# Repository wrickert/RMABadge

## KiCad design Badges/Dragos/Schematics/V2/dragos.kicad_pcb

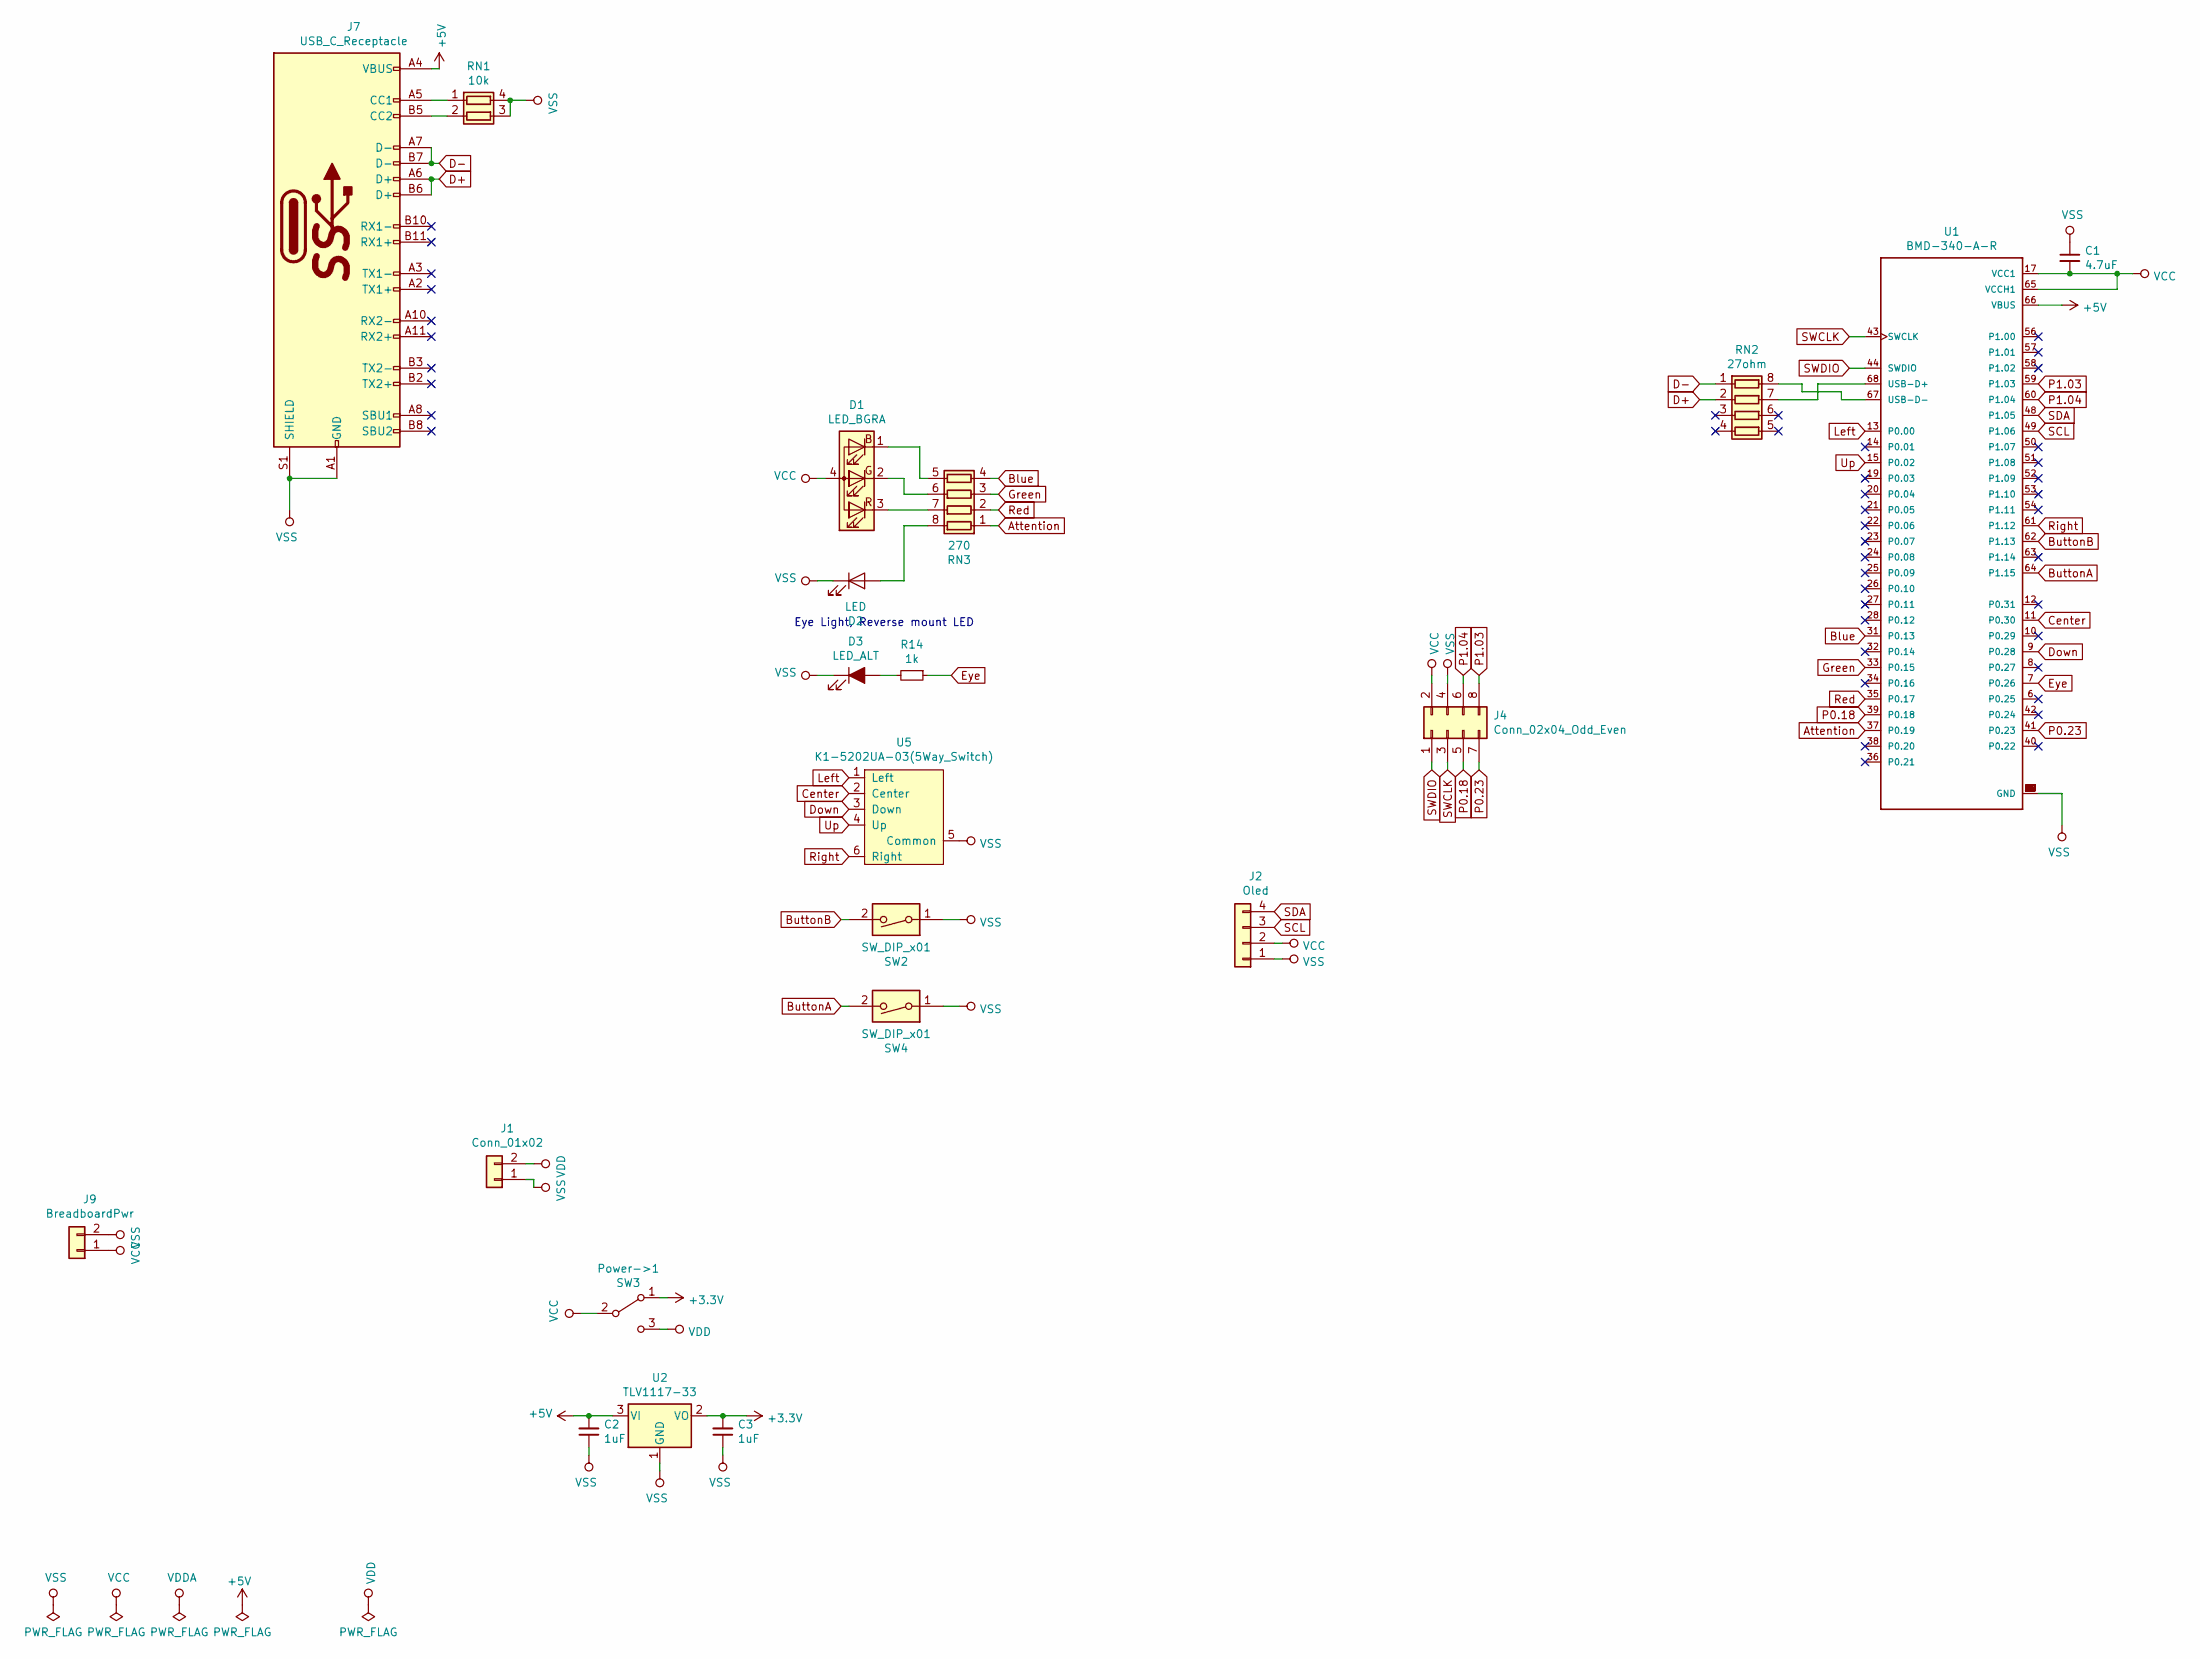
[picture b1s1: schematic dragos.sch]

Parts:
C1: 4.7uF; C_0805_2012Metric
C2, C3: 1uF; C_0805_2012Metric
D1: LED_BGRA; EKINGLUX-E6
D2: LED; LED_0603_1608Metric
D3: LED_ALT; T776-ReverseMountLED
J1: Conn_01x02
J2: Oled
J4: Conn_02x04_Odd_Even; PinHeader_2x04_P2.54mm_Vertical
J7: USB_C_Receptacle; USB_C_Receptical-Jing
J9: BreadboardPwr; PinHeader_1x02_P2.54mm_Vertical
Power->1: SW3; SK-3296S_switch
R14: 1k; R_0805_2012Metric
RN1: 10k; R_Array_Concave_2x0603
RN2: 27ohm; R_Array_Convex_4x0603
RN3: 270; R_Array_Convex_4x0603
SW2, SW4: SW_DIP_x01; 1TS002E-2500-2500-CT-HYP-Button
U1: BMD-340-A-R; RIGADO_BMD-340-A-R
U2: TLV1117-33; SOT-223-3_TabPin2
U5: K1-5202UA-03(5Way_Switch); K1-5202UA-03(5way-switch)

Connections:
+3V3: C3.2, Power->1.1 (A), U2.2 (VO)
+5V: C2.2, J7.A4 (VBUS), J7.A9 (VBUS), J7.B4 (VBUS), J7.B9 (VBUS), U1.66 (VBUS), U2.3 (VI)
Attention: RN3.1 (R1.1), U1.37 (P0.19)
Blue: RN3.4 (R4.1), U1.31 (P0.13)
ButtonA: SW4.2, U1.64 (P1.15)
ButtonB: SW2.2, U1.62 (P1.13)
Center: U1.11 (P0.30), U5.2 (Center)
D+: J7.A6 (D+), J7.B6 (D+), RN2.2 (R2.1)
D-: J7.A7 (D-), J7.B7 (D-), RN2.1 (R1.1)
Down: U1.9 (P0.28), U5.3 (Down)
Eye: R14.1, U1.7 (P0.26)
Green: RN3.3 (R3.1), U1.33 (P0.15)
Left: U1.13 (P0.00), U5.1 (Left)
unnamed: D1.1 (BK), RN3.5 (R4.2)
unnamed: D1.2 (GK), RN3.6 (R3.2)
unnamed: D1.3 (RK), RN3.7 (R2.2)
unnamed: D2.2 (A), RN3.8 (R1.2)
unnamed: D3.2 (A), R14.2
unnamed: J7.A5 (CC1), RN1.1 (R1.1)
unnamed: J7.B5 (CC2), RN1.2 (R2.1)
unnamed: RN2.7 (R2.2), U1.68 (USB-D+)
unnamed: RN2.8 (R1.2), U1.67 (USB-D-)
P0.18: J4.5, U1.39 (P0.18)
P0.23: J4.7, U1.41 (P0.23)
P1.03: J4.8, U1.59 (P1.03)
P1.04: J4.6, U1.60 (P1.04)
Red: RN3.2 (R2.1), U1.35 (P0.17)
Right: U1.61 (P1.12), U5.6 (Right)
SCL: J2.3, U1.49 (P1.06)
SDA: J2.4, U1.48 (P1.05)
SWCLK: J4.3, U1.43 (SWCLK)
SWDIO: J4.1, U1.44 (SWDIO)
Up: U1.15 (P0.02), U5.4 (Up)
VCC: C1.2, D1.4 (A), J2.2, J4.2, J9.1, Power->1.2 (B), U1.17 (VCC1), U1.65 (VCCH1)
VDD: J1.2, Power->1.3 (C)
VSS: C1.1, C2.1, C3.1, D2.1 (K), D3.1 (K), J1.1, J2.1, J4.4, J7.A1 (GND), J7.A12 (GND), J7.B1 (GND), J7.B12 (GND), J7.S1 (SHIELD), J9.2, RN1.3 (R2.2), RN1.4 (R1.2), SW2.1, SW4.1, U1.1 (GND), U1.2 (GND), U1.3 (GND), U1.4 (GND), U1.5 (GND), U1.16 (GND), U1.18 (GND), U1.29 (GND), U1.30 (GND), U1.45 (GND), U1.46 (GND), U1.47 (GND), U1.55 (GND), U2.1 (GND), U5.5 (Common)

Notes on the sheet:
Eye Light, Reverse mount LED

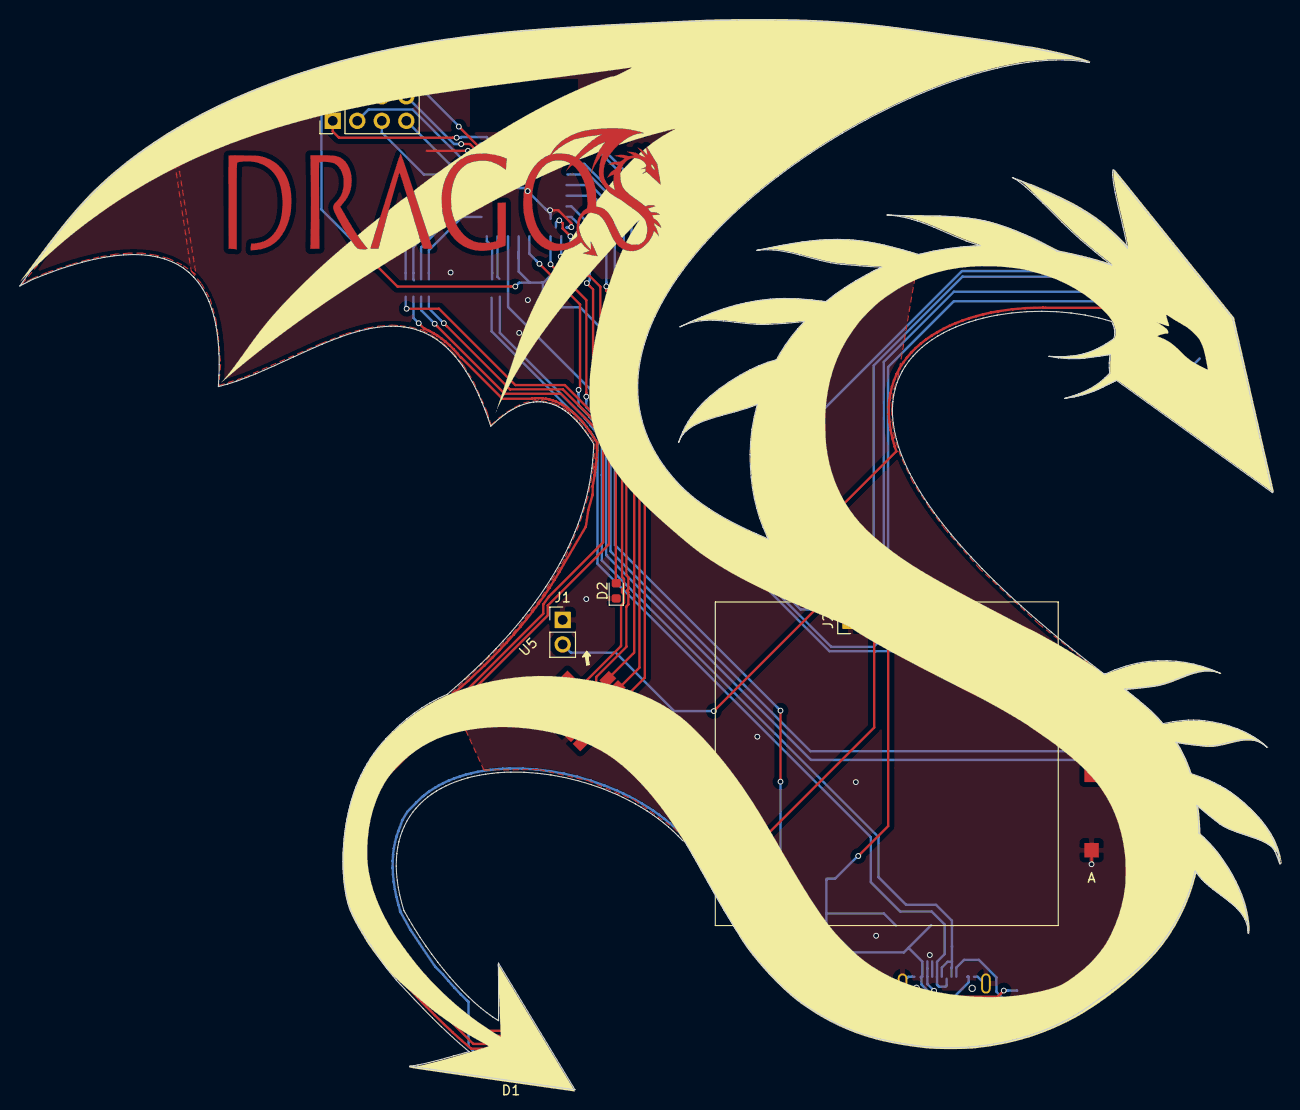
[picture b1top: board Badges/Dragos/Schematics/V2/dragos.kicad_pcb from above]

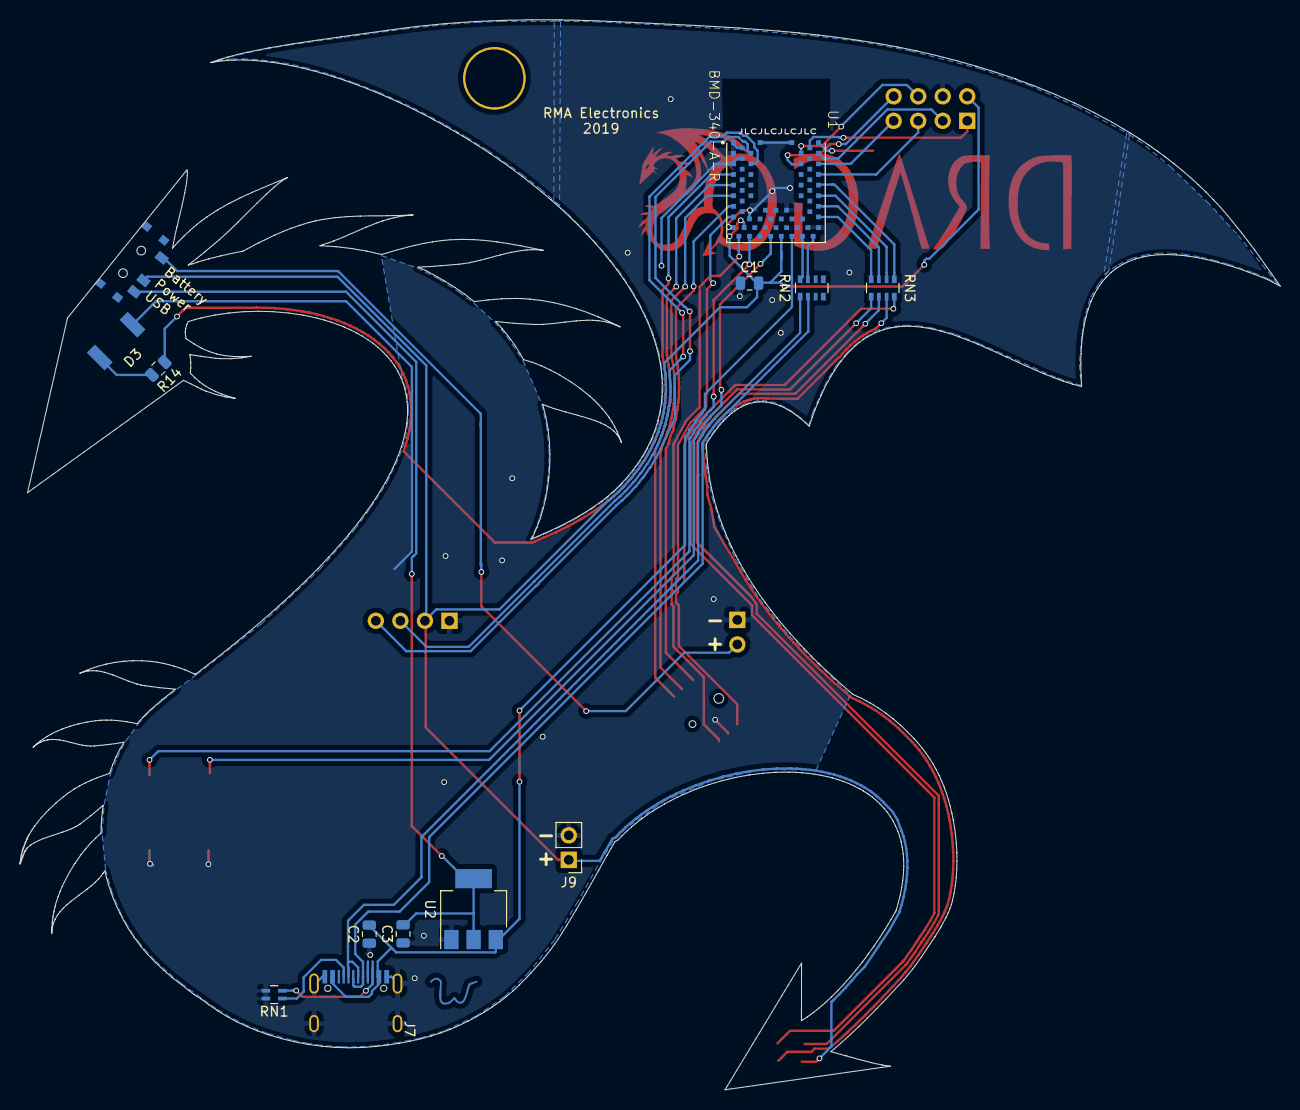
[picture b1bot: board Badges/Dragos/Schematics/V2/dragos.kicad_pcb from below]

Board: 2 copper layers, 130.4 x 110.8 mm, 22 parts (14 on the bottom side), 36 nets.

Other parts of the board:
Ref**: Val**; W

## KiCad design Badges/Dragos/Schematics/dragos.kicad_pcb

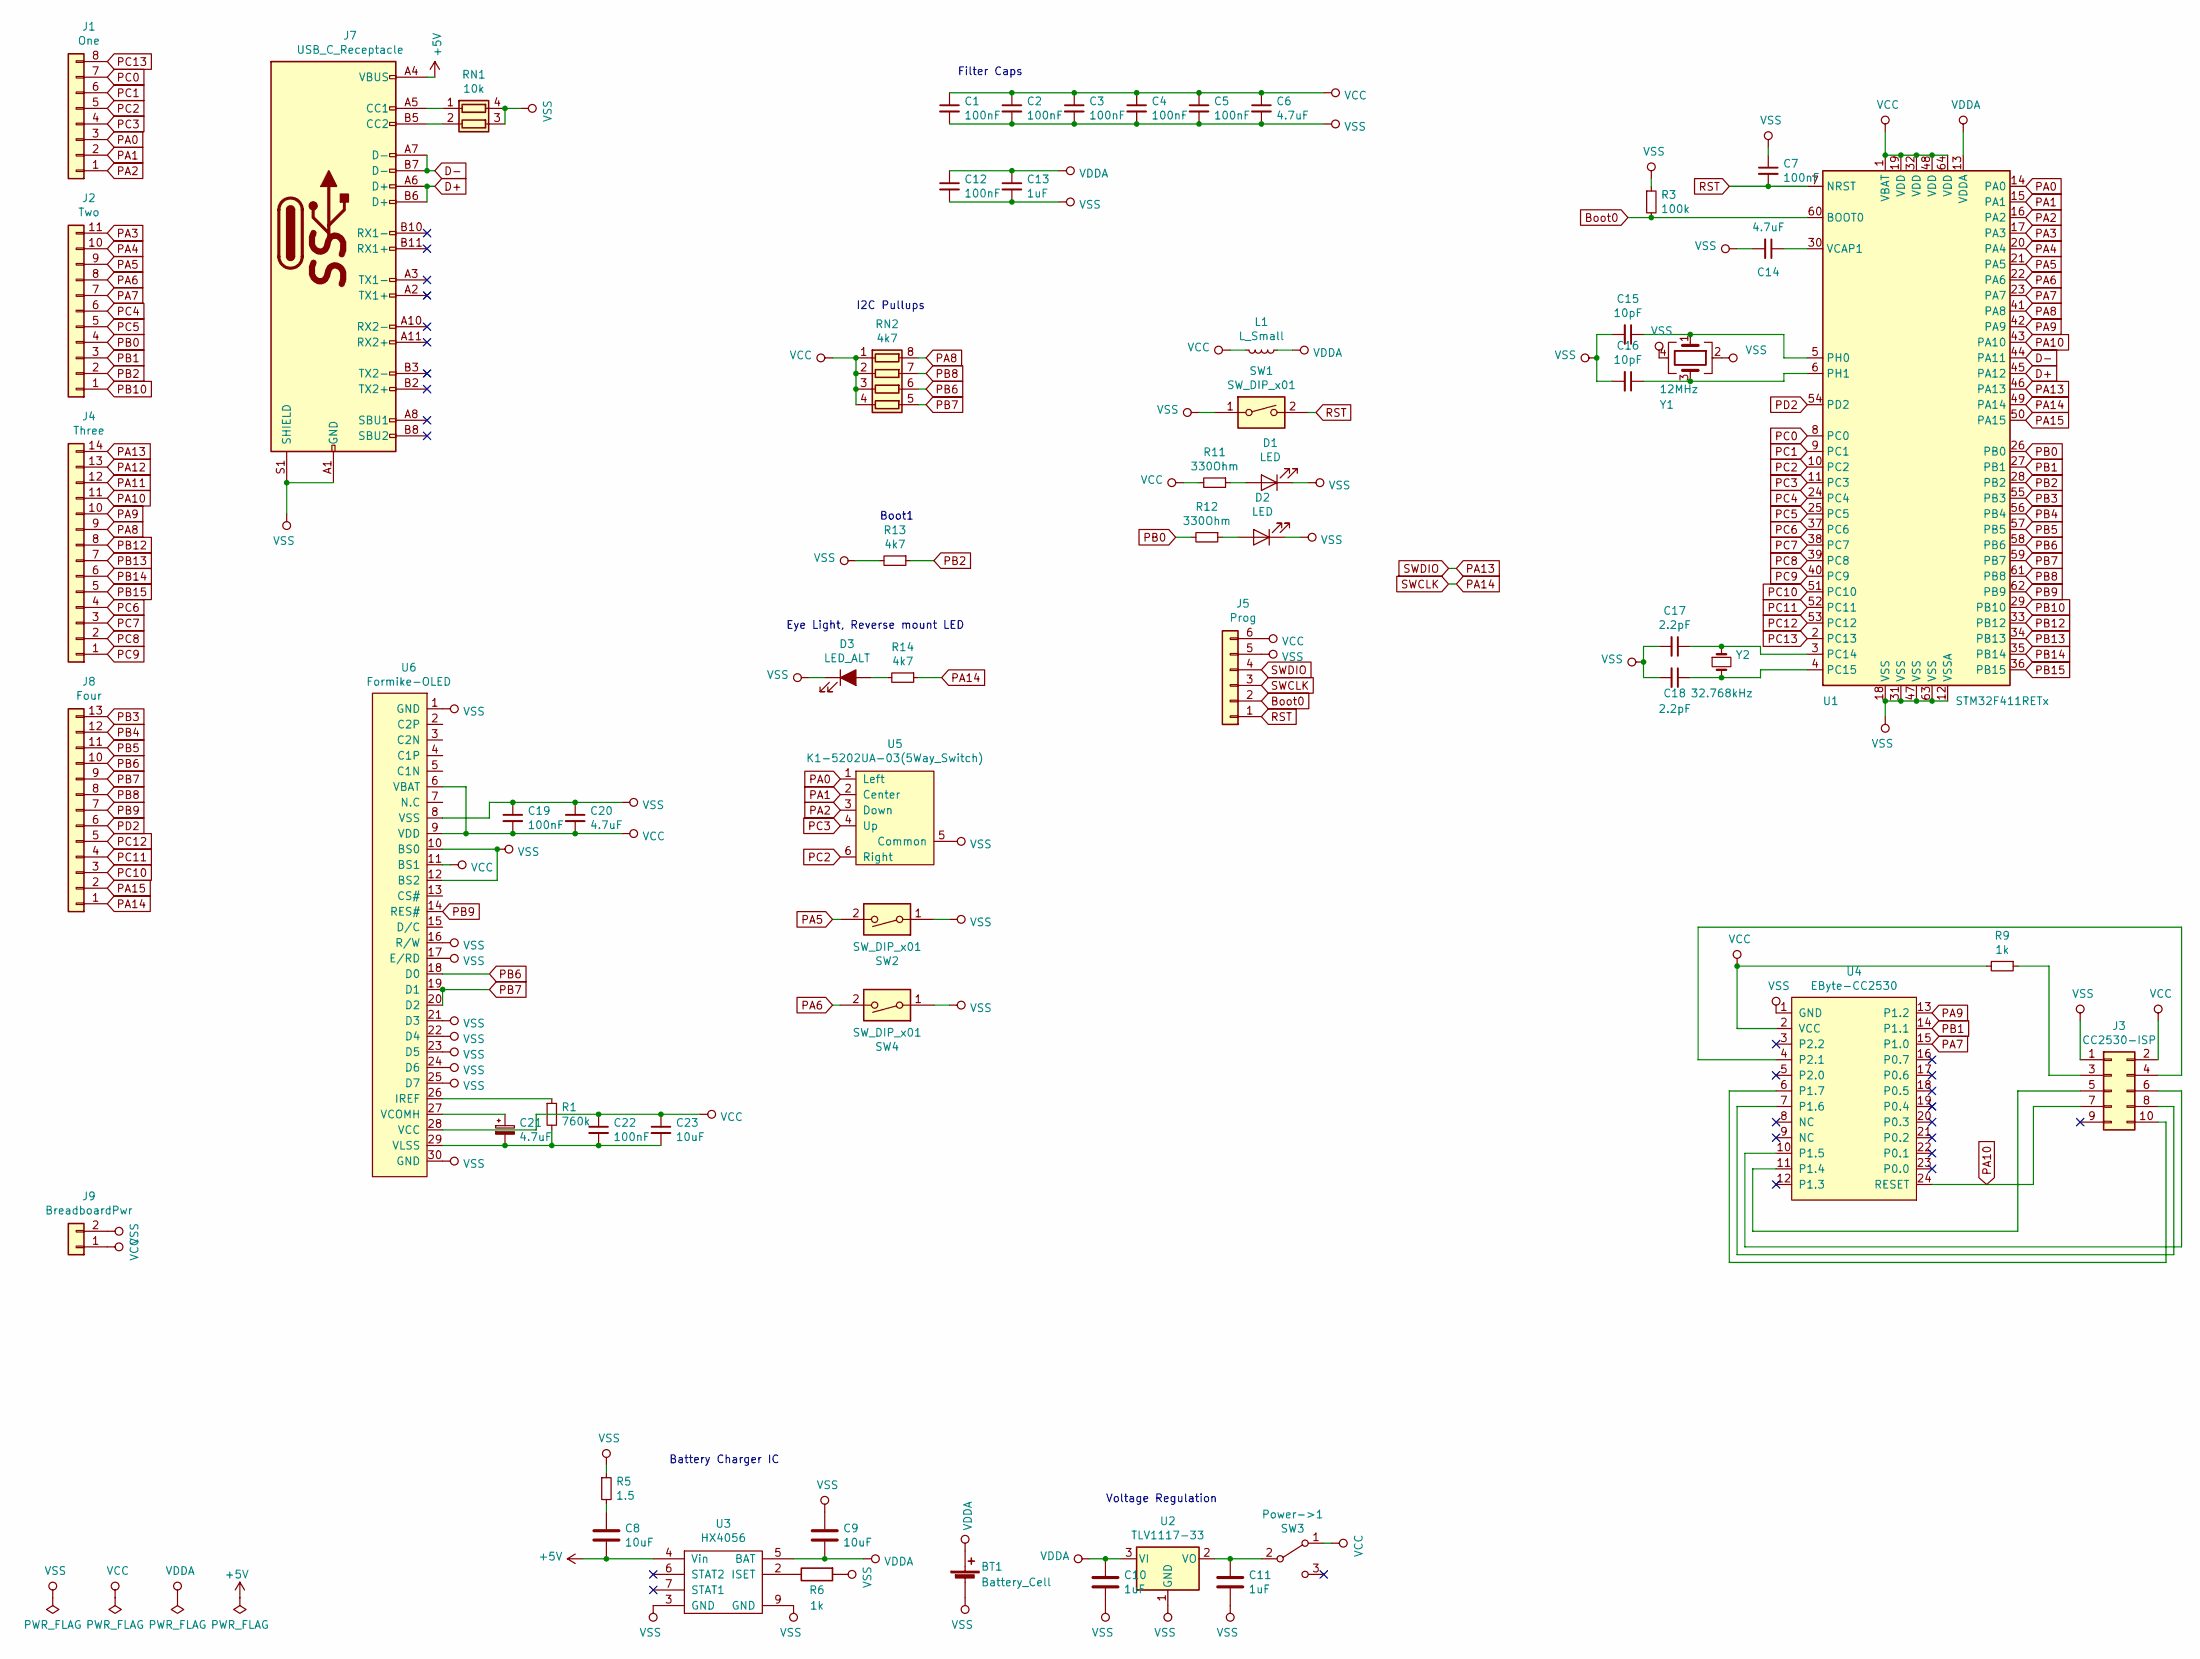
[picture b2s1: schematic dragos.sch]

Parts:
BT1: Battery_Cell; Dongguan14500
C1, C2, C3, C4, C5, C7, C12, C19, C22: 100nF; C_0805_2012Metric
C6, C14, C20: 4.7uF; C_0805_2012Metric
C8, C9, C23: 10uF; C_0805_2012Metric
C10, C11, C13: 1uF; C_0805_2012Metric
C15, C16: 10pF; C_0805_2012Metric
C17, C18: 2.2pF; C_0805_2012Metric
C21: 4.7uF; C_2010_5025Metric_Pad1.52x2.65mm_HandSolder
D1, D2: LED; LED_0603_1608Metric
D3: LED_ALT; T776-ReverseMountLED
J1: One; PinHeader_1x08_P2.54mm_Vertical
J2: Two; PinHeader_1x11_P2.54mm_Vertical
J3: CC2530-ISP; PinHeader_2x05_P1.00mm_Vertical
J4: Three; PinHeader_1x14_P2.54mm_Vertical
J5: Prog; PinHeader_1x06_P1.00mm_Vertical
J7: USB_C_Receptacle; USB_C_Receptical-Jing
J8: Four; PinHeader_1x13_P2.54mm_Vertical
J9: BreadboardPwr; PinHeader_1x02_P2.54mm_Vertical
L1: L_Small; L_0603_1608Metric
Power->1: SW3; SK-3296S_switch
R1: 760k; R_0805_2012Metric
R3: 100k; R_0805_2012Metric
R5: 1.5; R_0805_2012Metric
R6, R9: 1k; R_0805_2012Metric
R11, R12: 330Ohm; R_0805_2012Metric
R13, R14: 4k7; R_0805_2012Metric
RN1: 10k; R_Array_Concave_2x0603
RN2: 4k7; R_Array_Concave_4x0603
SW1: SW_DIP_x01; SW_Push_1P1T_NO_CK_KSC7xxJ
SW2, SW4: SW_DIP_x01; 1TS002E-2500-2500-CT-HYP-Button
U1: STM32F411RETx; LQFP-64_10x10mm_P0.5mm
U2: TLV1117-33; SOT-223-3_TabPin2
U3: HX4056; HSOP-8-1EP_3.9x4.9mm_P1.27mm_EP2.41x3.1mm
U4: EByte-CC2530; E18-MS1-PCB
U5: K1-5202UA-03(5Way_Switch); K1-5202UA-03(5way-switch)
U6: Formike-OLED; Hirose_FH12-30S-0.5SH_1x30-1MP_P0.50mm_Horizontal
Y1: 12MHz; Crystal_SMD_SeikoEpson_TSX3225-4Pin_3.2x2.5mm
Y2: 32.768kHz; Crystal_SMD_3215-2Pin_3.2x1.5mm

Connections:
+5V: C8.2, J7.A4 (VBUS), J7.A9 (VBUS), J7.B4 (VBUS), J7.B9 (VBUS), U3.4 (Vin)
Boot0: J5.2, R3.2, U1.60 (BOOT0)
D+: J7.A6 (D+), J7.B6 (D+), U1.45 (PA12)
D-: J7.A7 (D-), J7.B7 (D-), U1.44 (PA11)
unnamed: C8.1, R5.2
unnamed: C11.1, Power->1.2 (B), U2.2 (VO)
unnamed: C14.1, U1.30 (VCAP1)
unnamed: C15.1, U1.5 (PH0), Y1.1
unnamed: C16.1, U1.6 (PH1), Y1.3
unnamed: C17.1, U1.3 (PC14), Y2.1
unnamed: C18.1, U1.4 (PC15), Y2.2
unnamed: C21.1, U6.27 (VCOMH)
unnamed: C21.2, C22.2, C23.2, R1.2, U6.29 (VLSS)
unnamed: D1.2 (A), R11.1
unnamed: D2.2 (A), R12.1
unnamed: D3.2 (A), R14.2
unnamed: J3.3, R9.1
unnamed: J3.4, U4.4 (P2.1)
unnamed: J3.5, U4.11 (P1.4)
unnamed: J3.6, U4.10 (P1.5)
unnamed: J3.8, U4.7 (P1.6)
unnamed: J3.10, U4.6 (P1.7)
unnamed: J7.A5 (CC1), RN1.1 (R1.1)
unnamed: J7.B5 (CC2), RN1.2 (R2.1)
unnamed: R1.1, U6.26 (IREF)
unnamed: R6.1, U3.2 (ISET)
PA0: J1.3, U1.14 (PA0), U5.1 (Left)
PA1: J1.2, U1.15 (PA1), U5.2 (Center)
PA2: J1.1, U1.16 (PA2), U5.3 (Down)
PA3: J2.11, U1.17 (PA3)
PA4: J2.10, U1.20 (PA4)
PA5: J2.9, SW2.2, U1.21 (PA5)
PA6: J2.8, SW4.2, U1.22 (PA6)
PA7: J2.7, U1.23 (PA7), U4.15 (P1.0)
PA8: J4.9, RN2.8 (R1.2), U1.41 (PA8)
PA9: J4.10, U1.42 (PA9), U4.13 (P1.2)
PA10: J3.7, J4.11, U1.43 (PA10), U4.24 (RESET)
PA13: J4.14, J5.4, U1.46 (PA13)
PA14: J5.3, J8.1, R14.1, U1.49 (PA14)
PA15: J8.2, U1.50 (PA15)
PB0: J2.4, R12.2, U1.26 (PB0)
PB1: J2.3, U1.27 (PB1), U4.14 (P1.1)
PB2: J2.2, R13.1, U1.28 (PB2)
PB3: J8.13, U1.55 (PB3)
PB4: J8.12, U1.56 (PB4)
PB5: J8.11, U1.57 (PB5)
PB6: J8.10, RN2.6 (R3.2), U1.58 (PB6), U6.18 (D0)
PB7: J8.9, RN2.5 (R4.2), U1.59 (PB7), U6.19 (D1), U6.20 (D2)
PB8: J8.8, RN2.7 (R2.2), U1.61 (PB8)
PB9: J8.7, U1.62 (PB9), U6.14 (RES#)
PB10: J2.1, U1.29 (PB10)
PB12: J4.8, U1.33 (PB12)
PB13: J4.7, U1.34 (PB13)
PB14: J4.6, U1.35 (PB14)
PB15: J4.5, U1.36 (PB15)
PC0: J1.7, U1.8 (PC0)
PC1: J1.6, U1.9 (PC1)
PC2: J1.5, U1.10 (PC2), U5.6 (Right)
PC3: J1.4, U1.11 (PC3), U5.4 (Up)
PC4: J2.6, U1.24 (PC4)
PC5: J2.5, U1.25 (PC5)
PC6: J4.4, U1.37 (PC6)
PC7: J4.3, U1.38 (PC7)
PC8: J4.2, U1.39 (PC8)
PC9: J4.1, U1.40 (PC9)
PC10: J8.3, U1.51 (PC10)
PC11: J8.4, U1.52 (PC11)
PC12: J8.5, U1.53 (PC12)
PC13: J1.8, U1.2 (PC13)
PD2: J8.6, U1.54 (PD2)
RST: C7.2, J5.1, SW1.2, U1.7 (NRST)
VCC: C1.1, C2.1, C3.1, C4.1, C5.1, C6.1, C19.2, C20.2, C22.1, C23.1, J3.2, J5.6, J9.1, L1.2, Power->1.1 (A), R9.2, R11.2, RN2.1 (R1.1), RN2.2 (R2.1), RN2.3 (R3.1), RN2.4 (R4.1), U1.1 (VBAT), U1.19 (VDD), U1.32 (VDD), U1.48 (VDD), U1.64 (VDD), U4.2 (VCC), U6.6 (VBAT), U6.9 (VDD), U6.11 (BS1), U6.28 (VCC)
VDDA: BT1.1 (+), C9.2, C10.1, C12.1, C13.1, L1.1, U1.13 (VDDA), U2.3 (VI), U3.5 (BAT)
VSS: BT1.2 (-), C1.2, C2.2, C3.2, C4.2, C5.2, C6.2, C7.1, C9.1, C10.2, C11.2, C12.2, C13.2, C14.2, C15.2, C16.2, C17.2, C18.2, C19.1, C20.1, D1.1 (K), D2.1 (K), D3.1 (K), J3.1, J5.5, J7.A1 (GND), J7.A12 (GND), J7.B1 (GND), J7.B12 (GND), J7.S1 (SHIELD), J9.2, R3.1, R5.1, R6.2, R13.2, RN1.3 (R2.2), RN1.4 (R1.2), SW1.1, SW2.1, SW4.1, U1.12 (VSSA), U1.18 (VSS), U1.31 (VSS), U1.47 (VSS), U1.63 (VSS), U2.1 (GND), U3.3 (GND), U3.9 (GND), U4.1 (GND), U5.5 (Common), U6.1 (GND), U6.8 (VSS), U6.10 (BS0), U6.12 (BS2), U6.16 (R/W), U6.17 (E/RD), U6.21 (D3), U6.22 (D4), U6.23 (D5), U6.24 (D6), U6.25 (D7), U6.30 (GND), Y1.2, Y1.4

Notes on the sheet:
Filter Caps
I2C Pullups
Voltage Regulation
Battery Charger IC
Boot1
Eye Light, Reverse mount LED

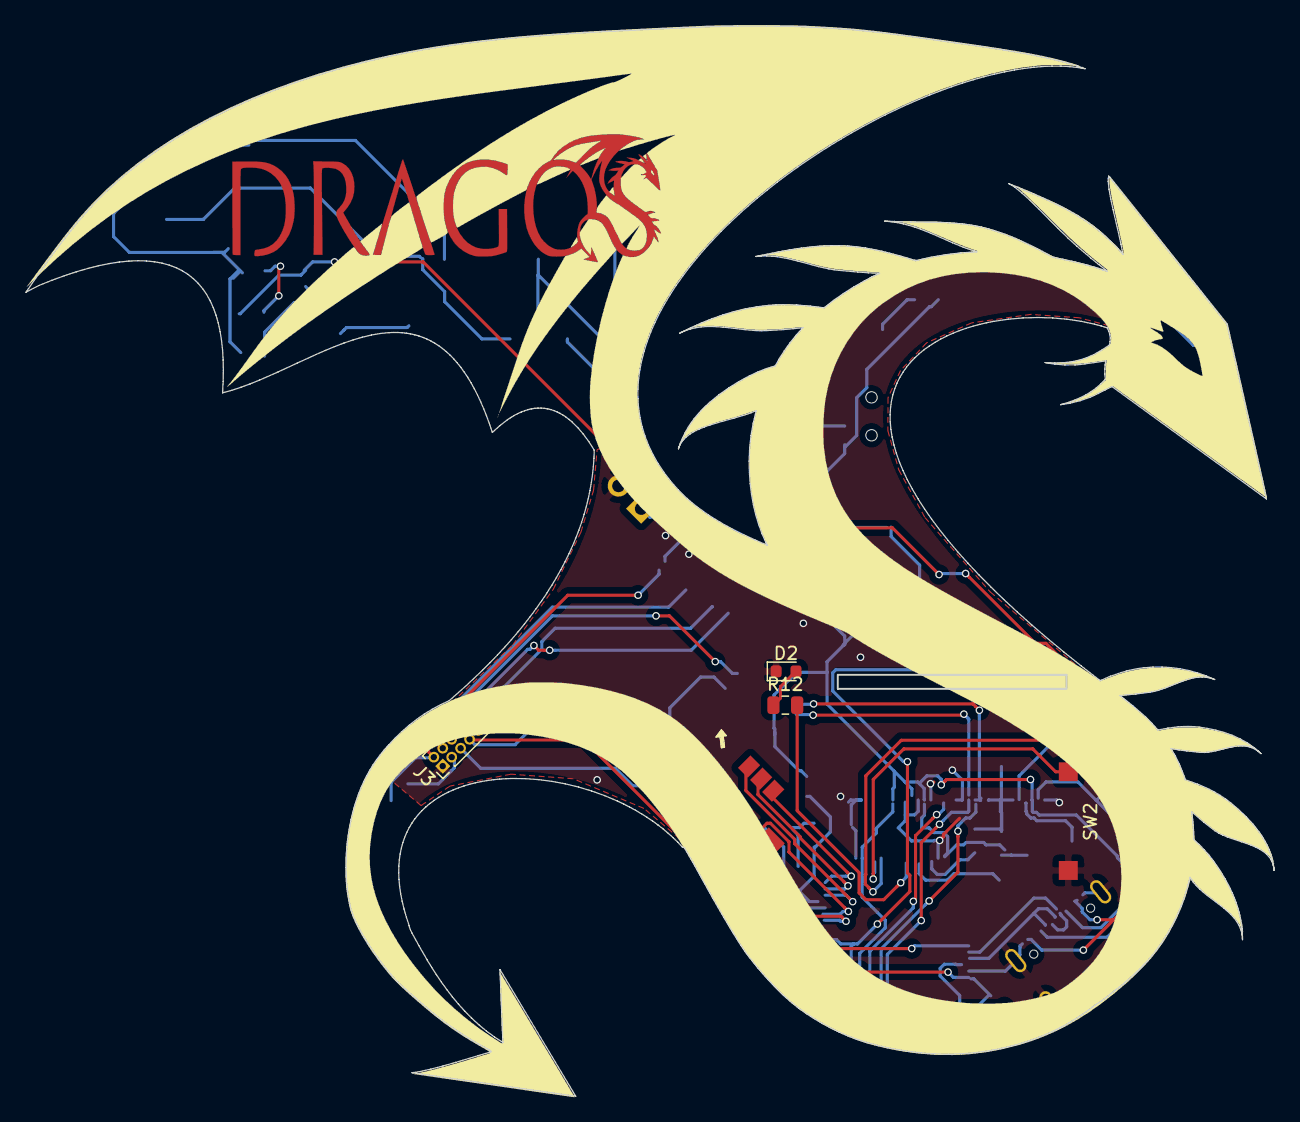
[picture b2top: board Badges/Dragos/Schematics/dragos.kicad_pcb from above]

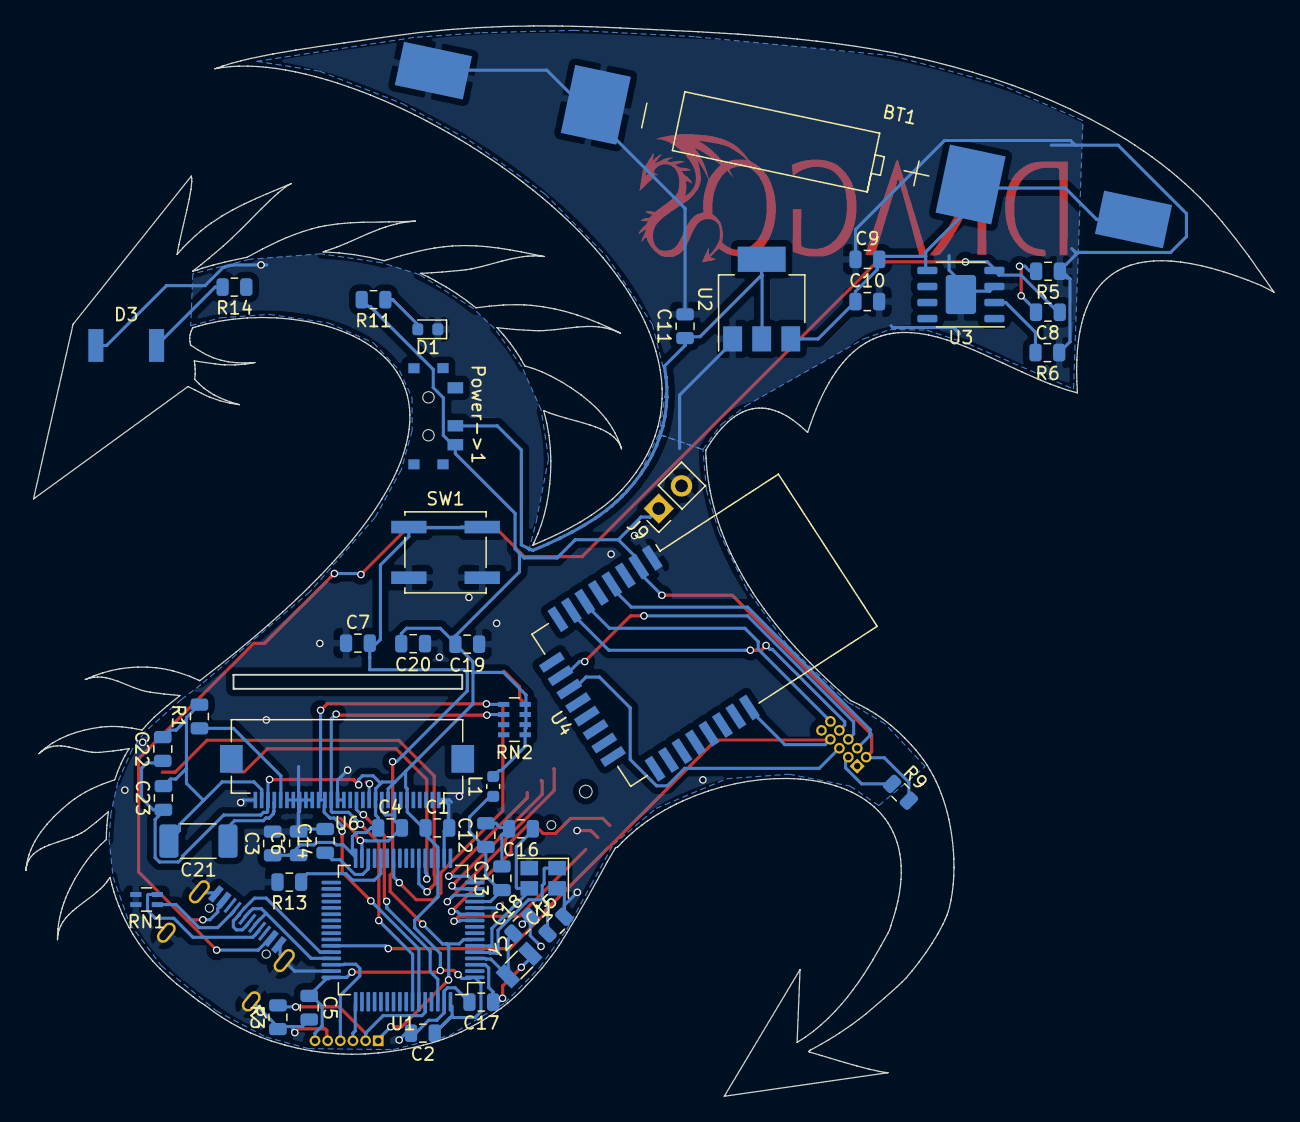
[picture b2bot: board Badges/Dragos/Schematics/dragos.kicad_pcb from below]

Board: 2 copper layers, 98.7 x 84.6 mm, 55 parts (48 on the bottom side), 50 nets.

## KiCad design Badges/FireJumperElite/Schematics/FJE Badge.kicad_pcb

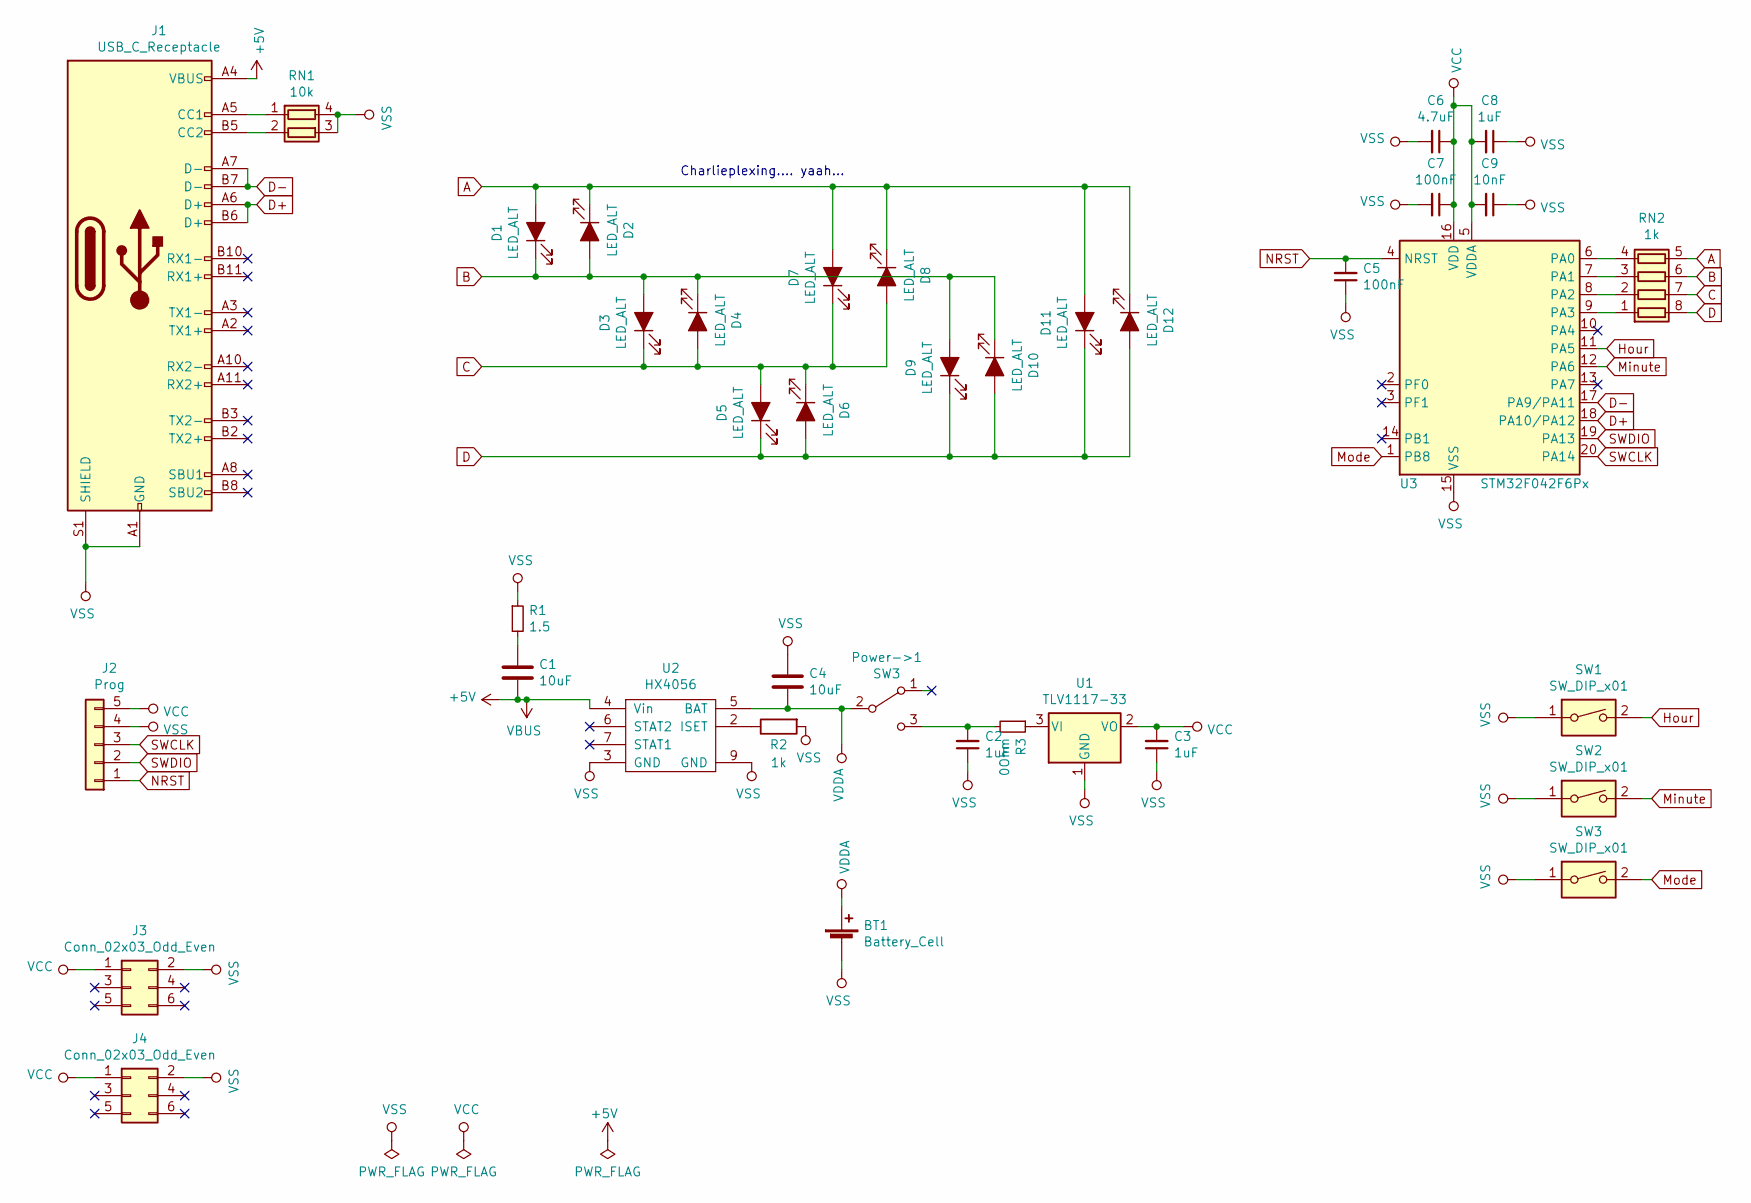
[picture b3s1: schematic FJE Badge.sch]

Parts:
BT1: Battery_Cell; BatteryHolder_Keystone_3008_1x2450
C1, C4: 10uF; C_0805_2012Metric
C2, C3, C8: 1uF; C_0805_2012Metric
C5, C7: 100nF; C_0805_2012Metric
C6: 4.7uF; C_0805_2012Metric
C9: 10nF; C_0805_2012Metric
D1, D2, D3, D4, D5, D6, D7, D8, D9, D10, D11, D12: LED_ALT; T776-ReverseMountLED
J1: USB_C_Receptacle; USB_C_Receptical-Jing
J2: Prog; PinHeader_1x05_P2.54mm_Vertical
J3, J4: Conn_02x03_Odd_Even; PinSocket_2x03_P2.54mm_Vertical
Power->1: SW3; SK-3296S_switch
R1: 1.5; R_0805_2012Metric
R2: 1k; R_0805_2012Metric
R3: 0Ohm; R_0805_2012Metric
RN1: 10k; R_Array_Concave_2x0603
RN2: 1k; R_Array_Convex_4x0603
SW1, SW2, SW3: SW_DIP_x01; SW_SPST_SKQG_WithStem
U1: TLV1117-33; SOT-223-3_TabPin2
U2: HX4056; HTSOP-8-1EP_3.9x4.9mm_P1.27mm_EP2.4x3.2mm
U3: STM32F042F6Px; TSSOP-20_4.4x6.5mm_P0.65mm

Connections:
+5V: C1.2, J1.A4 (VBUS), J1.A9 (VBUS), J1.B4 (VBUS), J1.B9 (VBUS), U2.4 (Vin)
A: D1.2 (A), D2.1 (K), D7.2 (A), D8.1 (K), D11.2 (A), D12.1 (K), RN2.5 (R4.2)
B: D1.1 (K), D2.2 (A), D3.2 (A), D4.1 (K), D9.2 (A), D10.1 (K), RN2.6 (R3.2)
C: D3.1 (K), D4.2 (A), D5.2 (A), D6.1 (K), D7.1 (K), D8.2 (A), RN2.7 (R2.2)
D: D5.1 (K), D6.2 (A), D9.1 (K), D10.2 (A), D11.1 (K), D12.2 (A), RN2.8 (R1.2)
D+: J1.A6 (D+), J1.B6 (D+), U3.18 (PA10/PA12)
D-: J1.A7 (D-), J1.B7 (D-), U3.17 (PA9/PA11)
Hour: SW1.2, U3.11 (PA5)
Minute: SW2.2, U3.12 (PA6)
Mode: SW3.2, U3.1 (PB8)
NRST: C5.2, J2.1, U3.4 (NRST)
unnamed: C1.1, R1.2
unnamed 12: C2.2, Power->1.3 (C), R3.2; also elsewhere on the board
unnamed: J1.A5 (CC1), RN1.1 (R1.1)
unnamed: J1.B5 (CC2), RN1.2 (R2.1)
unnamed: R2.1, U2.2 (ISET)
unnamed: R3.1, U1.3 (VI)
unnamed: RN2.1 (R1.1), U3.9 (PA3)
unnamed: RN2.2 (R2.1), U3.8 (PA2)
unnamed: RN2.3 (R3.1), U3.7 (PA1)
unnamed: RN2.4 (R4.1), U3.6 (PA0)
SWCLK: J2.3, U3.20 (PA14)
SWDIO: J2.2, U3.19 (PA13)
VCC: C3.2, C6.1, C7.1, C8.2, C9.2, J2.5, J3.1, J4.1, U1.2 (VO), U3.5 (VDDA), U3.16 (VDD)
VDDA: BT1.1 (+), C4.2, Power->1.2 (B), U2.5 (BAT); also elsewhere on the board
VSS: BT1.2 (-), C2.1, C3.1, C4.1, C5.1, C6.2, C7.2, C8.1, C9.1, J1.A1 (GND), J1.A12 (GND), J1.B1 (GND), J1.B12 (GND), J1.S1 (SHIELD), J2.4, J3.2, J4.2, R1.1, R2.2, RN1.3 (R2.2), RN1.4 (R1.2), SW1.1, SW2.1, SW3.1, U1.1 (GND), U2.3 (GND), U2.9 (GND), U3.15 (VSS)

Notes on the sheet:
Charlieplexing.... yaah...
